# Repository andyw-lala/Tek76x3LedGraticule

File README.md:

# Tek76x3LedGraticule
A project to retro-fit LED graticule lighting to Tektronix 76x3 scopes.

After retrofitting [LED graticule lighting in my 7904A](https://github.com/andyw-lala/Tek7904ALedGraticule) (which was in turn inspired by the white LED upgrade to a [Tek 7854 by Zenwizard Studios](https://youtu.be/GYkjuE7Pez8)), I decided to upgrade the graticule lights on my 7603 and 7633 scopes.

Attempts to take the simple route of just replacing the lamps with LEDs, as per [another excellent Zenwizard video](https://youtu.be/xNx9IgudV4Y) resulted in burnt out LEDs - eventually I added a dropping resistor, but was unhappy with the result - specifically the adjustment range, so I kept digging.
The control circuitry in the 76x3 scopes will current limit, so I initially investigated adjusting the current limit sense circuitry to limit the max current to a safe level for the LEDs, but that resulted in even less useful adjustment range from the front panel control.

Like the 7904A retrofit, this design completely replaces the existing incandescent graticule lamp driver circuit with a variable current source, while honoring the existing control mechanism.

## Theory of Operation

The 76x3 mainframes control the graticule illumination by means of a front panel variable resistor (R1095) and circuitry on the rectifier PCB (A11) at the rear of the unit. R1095 provides a voltage between -15V (graticule off) and +5V (graticule max). This voltage is applied to Q829, Q835, & Q827 and associated passives to provide a current limited variable voltage to three incandescent lamps that are wired in parallel. A single 4-way ribbon cable carries +15V, -15V, the control signal from R1095 and the output to the graticule lamp assembly (A13.) This cable mates with P891 on the rectifier board where the control circuit resides.

In a similar manner to the 7904A retrofit, the replacement circuit uses the same control signal (-15 to +5 volts) to control an approximately 0 - 20 mA current to ground that is used to drive the LEDs, which are re-wired to be in series.

The -15 to +5V control voltage from R1095 drives the base of T1, resulting in a 0 - 4 mA T1 collector current. In order drive a current to ground and preserve the nature of the graticule lamp assembly connections, this 0 - 4 mA control current is mirrored by T2, T3, & T4 acting as a [Wilson current mirror](https://en.wikipedia.org/wiki/Wilson_current_mirror), however due to the differing values of R3 & R4, the resultant current between the collector of T4 and ground varies between 0 and approximately 20 mA. As in the 7904A retrofit design, the exact fidelity of the current mirror is not important, so discrete, unmatched transistors are used.

Since all the required signals are present on the ribbon cable that normally connects to P891 on the rectifier board, a small PCB was designed to accept the ribbon cable instead. Installation comprises of removing the ribbon connection to P891 (which can be done without removing the power supply assembly from the case.)

The graticule light assembly is modified to replace the lamps with wide angle white LEDs,and to wire the LEDs in series.

## [Schematic](V1.pdf) (pdf)

## [BOM](BOM.md)

## Eagle Files
* [Schematic](V1.sch)
* [Board](V1.brd)

## Gerber Files
Here are generated gerbers, so you can use your PCB house of choice.
Note that I have only checked these with a viewer, I ordered my boards direct from OSHPark using the eagle board file. Send feedback if you use these files and they work or don't work.
* [Gerber zipfile](V1_gerbers.zip)

## Order Boards
You can order multiples of three known good boards directly from [OSHpark](https://oshpark.com/shared_projects/Er36gqKW).

## Installation
After assembling the board, installation consists of the following steps:
* Disconnection of P891 4-pin connector from rectifier board, and re-routing of 4-conductor ribbon cable.
* Removal, rework, and re-installation of graticule lamp assembly.
* Mounting of new PCB in a suitable location.
* Connection of P891 4-pin connector to new PCB.
### Disconnection of P891 from rectifier board
It is possible to unplug the 4-pin ribbon cable that plugs into P891 on the rectifier board without removal of the rectifier board and transformer assembly. With the power off, everything discharged, and the left cover removed; it is possible to work a narrow screwdriver or other tool in from the left hand side to work the connector loose while gently pulling on the ribbon cable. Once the connector is free of the rectifier board, gently untangle it from all the other ribbon and coax cables in the vicinity, to gain the maximum working length. Take care not to force other cables into the path of the fan which is nearby in some models.
### Removal of existing graticule lamp assembly
On the 7603, the graticule lamp assembly is mounted vertically to the left of the CRT. Remove the two knurled screws to the left of the CRT, and gently remove the front bezel and implosion shield. There should be a white diffuser (as shown [around here in Zen's youtube video](https://youtu.be/xNx9IgudV4Y?t=40).) Remove this and the spring that holds it in place. Remove the two mounting screws that bolt the assembly to the chassis, and work the existing lamp assembly free from the back. You can either rework the assembly while it is still connected to the scope, or remove it from the scope by unplugging the 2 pin connector from the calibrator board.
### Reworking the graticule lamp assembly
Remove the lamps, and cut or desolder the wires that connect the 3 lamp sockets.
At this point you can trim the existing lamp sockets back so that they will not touch the chassis, if you wish (more on this later.) I found passing the LED positive leg (the long lead in the specified parts) through the hole in the center connector of the socket, soldering it in place and then soldering the negative leg to the outside connector of the lamp socket worked well. Wire the sockets in series using any suitable hookup wire.

Note that the outside conductor of the lamp sockets can, and most likely will, be grounded by contact with the chassis when the assembly is in place, this will cause one or more LEDs not to light, no damage will occur as the current is limited to ~20mA, but the lighting is uneven and very poor. This is why I suggest trimming the metal of the lamp sockets back, but for my first 7603 rework, I used kapton tape to insulate the lamp sockets.

### Reinstallation of graticule lamp assembly
The graticule lamp assembly is installed by reversing the steps for removal. Note that depending on how far the LEDs protrude through the chassis, the registration of the diffuser may not be quite as positive, but it has not been a problem in my experience.

Feel free to test at this point, but only if you are experienced enough to operate the scope with the side cover removed. Simply plug the ribbon cable into the PCB (pay close attention to orientation) while ensuring that the PCB is not touching any parts of the scope.

If none of the LEDs light, try reversing the 2-pin connector between the graticule lamp assembly and the calibrator board.

If one or more, but not all, of the LEDs light, then you have a short to chassis ground at the lamp assembly.

You should be able to vary the LED brightness using the normal front panel control and the diffuser should spread the light fairly evenly across the face of the CRT.

### Mounting new PCB in a suitable location
You are free to mount the PCB wherever you can find a suitable stable mechanical mounting point that the ribbon cable will reach. I ended up carefully drilling a suitable hole for a machine screw in the left side wall of the transformer/rectifier assembly. I was careful to remove all swarf immediately after drilling the hole with a vacuum and a brush. After struggling to hold a nut in place with the board in place, I resorted to installing a threaded bushing on the PCB.

I recommend mounting the PCB so that if the mounting bolt works loose and the board rotates, it is unable to rotate far enough to short pins to the chassis.

I also applied some additional kapton tape to the inside of the side cover, to reduce the chance of shorts if the side cover was pressed at just the wrong place.

The mounting location for the PCB is completely non-critical, as long as it is safe, mechanically sound, and the ribbon cable can reach. Feel free to devise your own arrangement (pull requests with alternate ideas welcome.)

### Connection of P891 4-pin connector to new PCB
When connecting the 4-pin connector that used to go to the rectifier board, play close attention to the orientation. Pin 1 is clearly marked on the PCB, line the arrow on the connector up with the pin that the arrow on the PCB points to.

### Final testing
Close up the case, ensure all cables are dressed well, and none are in the way of the fan, and perform a final test after the covers are all buttoned up.

# Licence
All work here is covered by the MIT Licence, which is simple and permissive.

# Disclaimer
This mod worked well for me, and is presented here in the hope it can be as useful to others. However, do not undertake this unless you have the skills to perform the work safely and without damaging anything. You perform all work at your own risk, and I have no responsibility for any damage or injury whatsoever.

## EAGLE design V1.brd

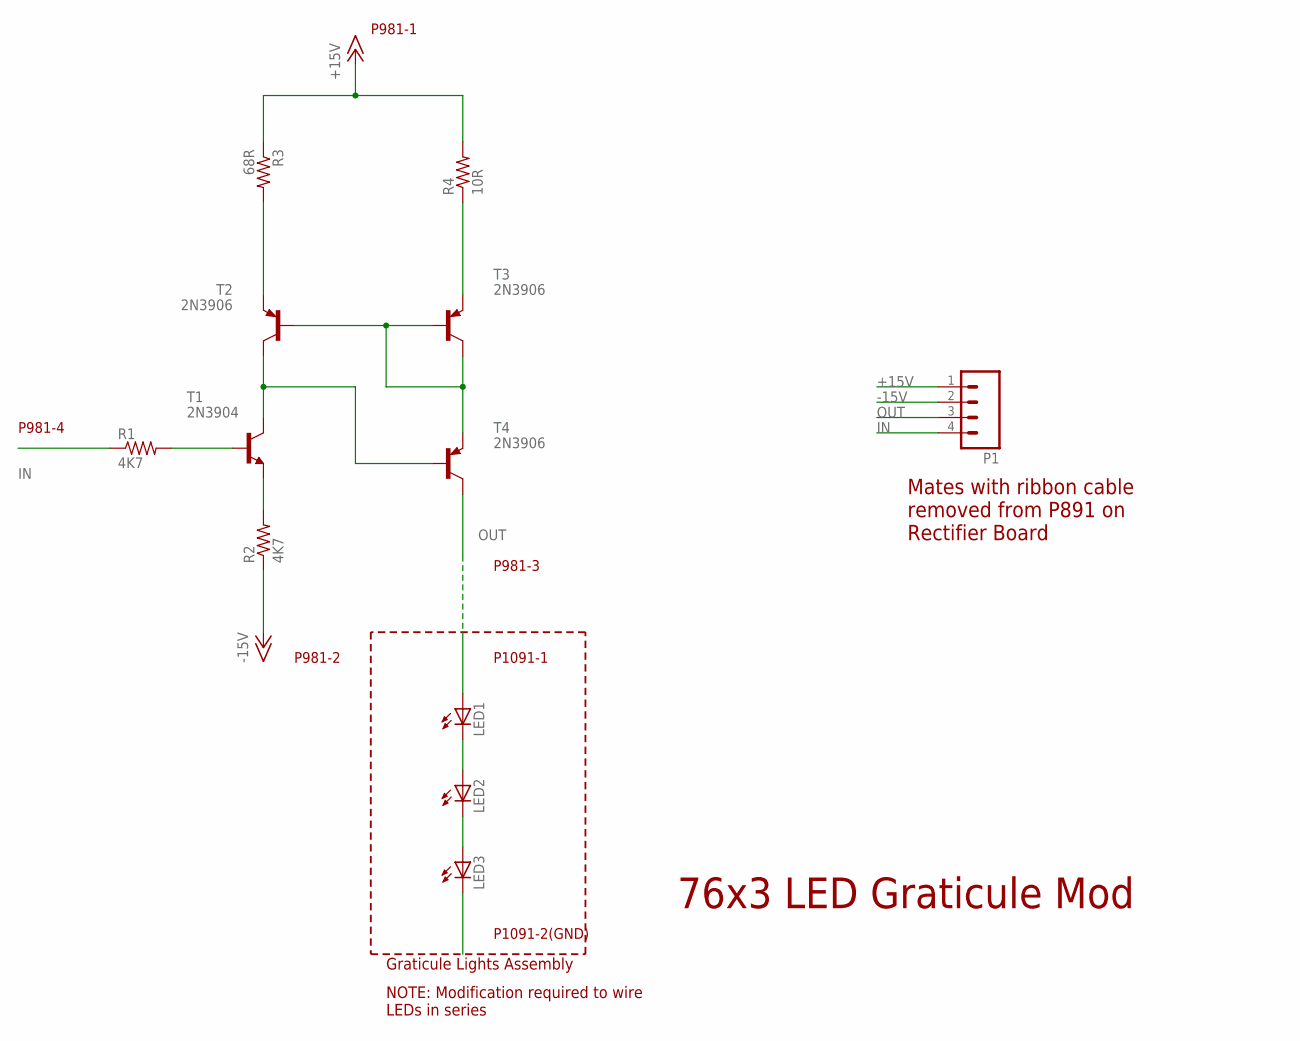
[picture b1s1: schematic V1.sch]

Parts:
LED1, LED2, LED3: LED5MM
P1: M04PTH; 1X04
R1, R2: 4K7; 0309V
R3: 68R; 0309V
R4: 10R; 0309V
T1: 2N3904; TO92-EBC
T2, T3, T4: 2N3906; TO92-EBC

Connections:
+15V: P1.1, R3.1, R4.2
-15V: P1.2, R2.1
IN: P1.4, R1.1
unnamed: R1.2, T1.B
unnamed: R2.2, T1.E
unnamed: R3.2, T2.E
unnamed: LED2.K (C), LED3.A
unnamed: LED1.K (C), LED2.A
unnamed: R4.1, T3.E
unnamed: T2.B, T3.B, T3.C, T4.E
unnamed: T1.C, T2.C, T4.B
OUT: P1.3, T4.C

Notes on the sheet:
P1091-2(GND)
P1091-1
P981-3
P981-4
76x3 LED Graticule Mod
Graticule Lights Assembly
NOTE: Modification required to wire LEDs in series
P981-1
P981-2
Mates with ribbon cable removed from P891 on Rectifier Board

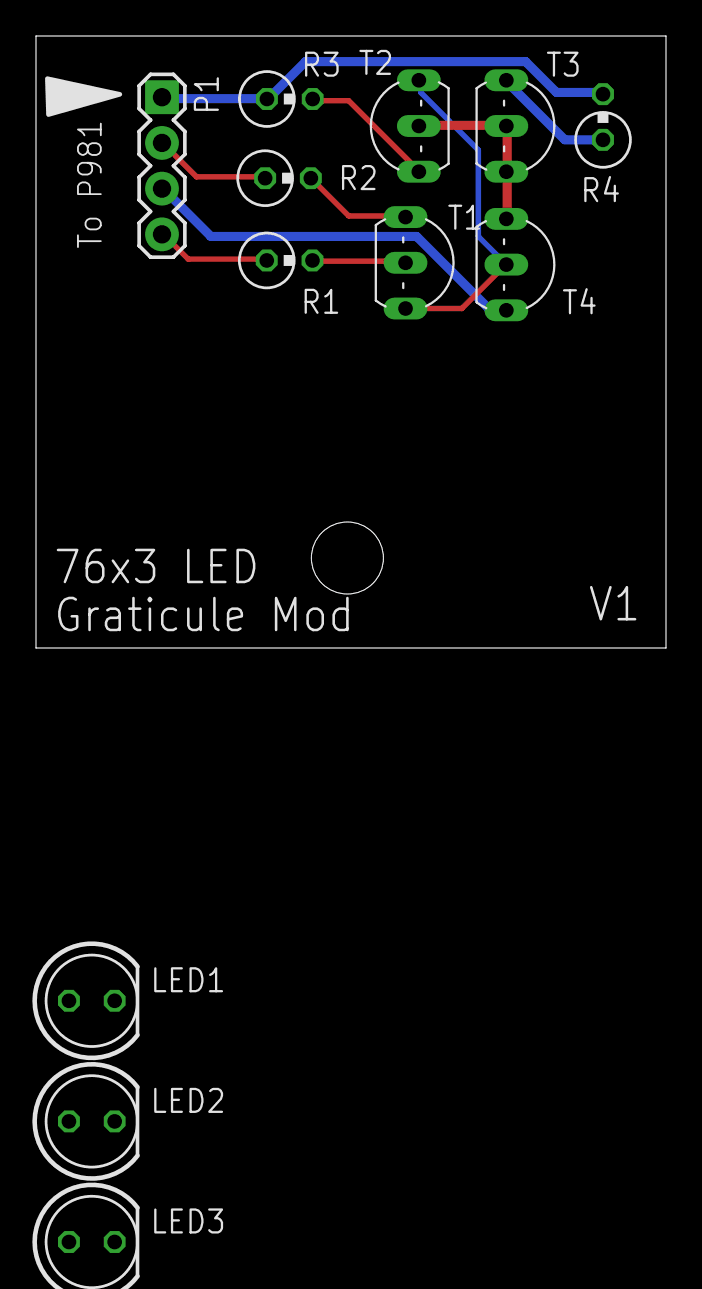
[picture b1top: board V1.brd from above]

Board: 2 copper layers, 35.0 x 34.0 mm, 12 parts (0 on the bottom side), 12 nets.

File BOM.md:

# BOM
![Schematic](images/V1.png)
Designator | Value | Description
---------- | ----- | -----------
LED1 | C535A-WJN-CT0W0231 | 5mm Cool White LED, 110 degrees
LED2 | C535A-WJN-CT0W0231 | 5mm Cool White LED, 110 degrees
LED3 | C535A-WJN-CT0W0231 | 5mm Cool White LED, 110 degrees
P1 | 4 pin 0.1" header |
R1 | 4K7 | 1/4W 5%
R2 | 4K7 | 1/4W 5%
R3 | 68R | 1/4W 5%
R4 | 10R | 1/4W 5%
T1 | 2N3904 | NPN
T2 | 2N3906 | PNP
T3 | 2N2906 | PNP
T4 | 2N2906 | PNP

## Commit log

2022-07-26 Initial checkin of WIP README.
2022-07-26 Add initial after photo.
2022-07-26 76x3 README
2022-07-26 Minor copy edit tweakage.
2022-07-26 sensing -> sense
2022-07-26 More copy edit fodder.
2022-07-26 More edit cleanup.
2022-07-26 Add schematic, and further README cleanup.
2022-07-26 Add BOM & image of schematic.
2022-07-26 Add eagle files.
2022-07-26 Add gerbers
2022-07-26 Add original schematic excerpt and new schematic for reference.
2022-07-26 Fixup alignment after schematic images.
2022-07-26 Add OSHPark link.
2022-07-28 Fix minor typo
2022-08-21 Add installation photos.
2022-08-21 Add installation/test instructions.
2022-08-21 Minor corrections.
2022-08-21 More minor corrections.
2023-09-24 Fix spelling mistake
2023-09-24 Clarify that fan is optional in the mainframe.

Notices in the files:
parts and their libraries:
SparkFun-Connectors: Licensing: Creative Commons ShareAlike 4.0 International - https://creativecommons.org/licenses/by-sa/4.0
